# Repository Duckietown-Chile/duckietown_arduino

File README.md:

# duckietown_arduino

Arduino based controller for Dukietown robots. This library is based on [serial_dxl](https://github.com/rorromr/serial_dxl).

* Microcontroller: ATmega 168 3.3V 8MHz
* Board: Arduino Pro Mini
* H Bridge: Double L9110

| Pin |   Function  |
|-----|-------------|
| 5   | PWM CHA-1B  |
| 6   | PWM CHB-1B  |
| 11  | PWM CHA-1A  |
| 12  | PWM CHB-1A  |

Registros:

| Address |   Type   | Size | Function                   |
|---------|----------|------|----------------------------|
| 6       | uint8_t  | 1    | LED (0: off, 1: on)        |
| 7       | int16_t  | 2    | PWM channel 1 (-255 to 255)|
| 9       | int16_t  | 2    | PWM channel 1 (-255 to 255)|

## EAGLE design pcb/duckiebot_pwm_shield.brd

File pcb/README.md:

# Duckiebot Shield

Raspberry Pi 3 Shied thats provide serial communication with Arduino ProMini 328.
Used in Duckiebot for motors and others sensors communication and control.

![duckiebot shield][duckiebotshield]

[duckiebotshield]: https://github.com/Duckietown-Chile/duckietown_arduino/blob/master/img/DuckiebotShield.png

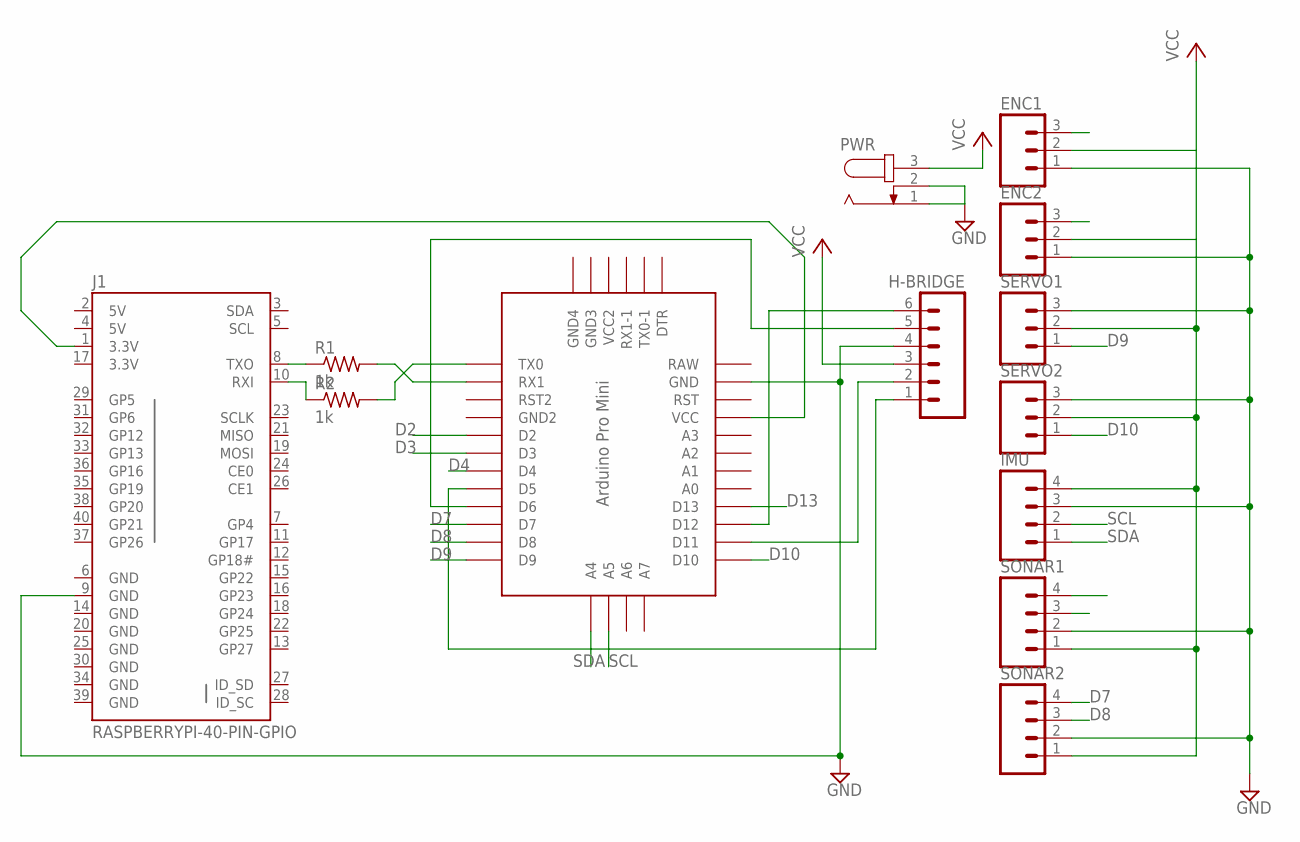
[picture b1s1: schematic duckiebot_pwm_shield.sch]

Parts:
ENC1, ENC2: M03LONGPADS; 1X03_LONGPADS
H-BRIDGE: M06LONGPADS; 1X06_LONGPADS
IMU: M04LONGPADS; 1X04_LONGPADS
J1: RASPBERRYPI-40-PIN-GPIO; 2X20-SHROUDED
PWR: JACK-PLUG0; SPC4077
R1, R2: 1k; 0309/10
SERVO1, SERVO2: M03LONGPADS; 1X03_LONGPADS
SONAR1, SONAR2: M04LONGPADS; 1X04_LONGPADS
U$2: PRO-MINI

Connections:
3.3V: J1.1 (3.3V), J1.17 (3.3V), U$2.VCC
5V: J1.2 (5V), J1.4 (5V)
A-1A: H-BRIDGE.2, U$2.D11
A-1B: H-BRIDGE.1, U$2.D5
B-1A: H-BRIDGE.6, U$2.D12
B-1B: H-BRIDGE.5, U$2.D6
D2: ENC1.3, U$2.D2
D3: ENC2.3, U$2.D3
D4: SONAR1.3, U$2.D4
D7: SONAR2.4, U$2.D7
D8: SONAR2.3, U$2.D8
D9: SERVO1.1, U$2.D9
D10: SERVO2.1, U$2.D10
D13: SONAR1.4, U$2.D13
GND: ENC1.1, ENC2.1, H-BRIDGE.4, IMU.3, J1.6 (GND), J1.9 (GND), J1.14 (GND), J1.20 (GND), J1.25 (GND), J1.30 (GND), J1.34 (GND), J1.39 (GND), PWR.1, PWR.2, SERVO1.3, SERVO2.3, SONAR1.2, SONAR2.2, U$2.GND
unnamed: R1.2, U$2.RX1
unnamed: R2.2, U$2.TX0
unnamed: J1.10 (RXI), R2.1
unnamed: J1.8 (TXO), R1.1
RAW: U$2.RAW
SCL: IMU.2, U$2.A5
SDA: IMU.1, U$2.A4
VCC: ENC1.2, ENC2.2, H-BRIDGE.3, IMU.4, PWR.3, SERVO1.2, SERVO2.2, SONAR1.1, SONAR2.1

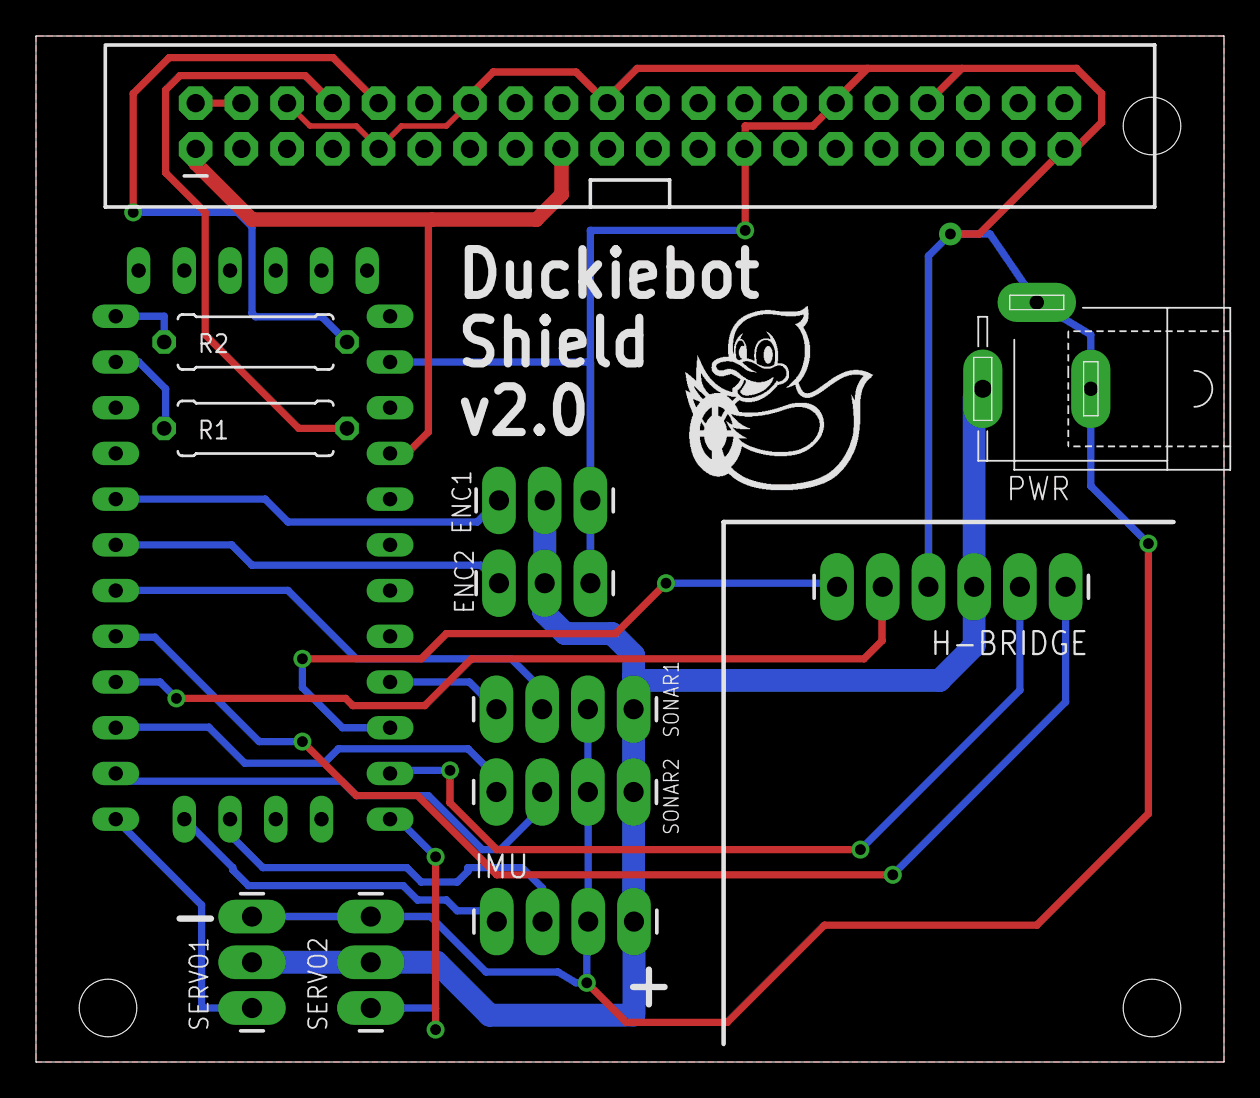
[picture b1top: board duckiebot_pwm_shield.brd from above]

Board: 2 copper layers, 66.0 x 57.0 mm, 14 parts (0 on the bottom side), 22 nets.

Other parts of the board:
U$1: DUCK_LOGO

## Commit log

2017-01-09 Blink example
2017-01-10 Test PWM
2017-01-10 Fix type
2017-01-11 Update duck script
2017-01-11 Basic doc
2017-01-17 eeprom and null reset functions
2017-01-17 Mount images
2017-01-17 Fix variables
2017-01-17 Fix doc
2017-01-18 duckiebot pcb v1.0
2017-01-20 Fix baudrate for ATmega168
2017-01-20 Fix pwm condition
2017-01-23 duckiebot shield updated v1.1
2017-01-23 duckiebot shield v1.2, duck missing :(
2017-01-23 v1.3, falta arreglar el layer del pato ql
2017-01-24 fixed resistor size, v1.4 ready to build
2017-03-13 added pcb image

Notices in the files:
parts and their libraries:
SparkFun-Boards: Licensing: Creative Commons ShareAlike 4.0 International - https://creativecommons.org/licenses/by-sa/4.0
